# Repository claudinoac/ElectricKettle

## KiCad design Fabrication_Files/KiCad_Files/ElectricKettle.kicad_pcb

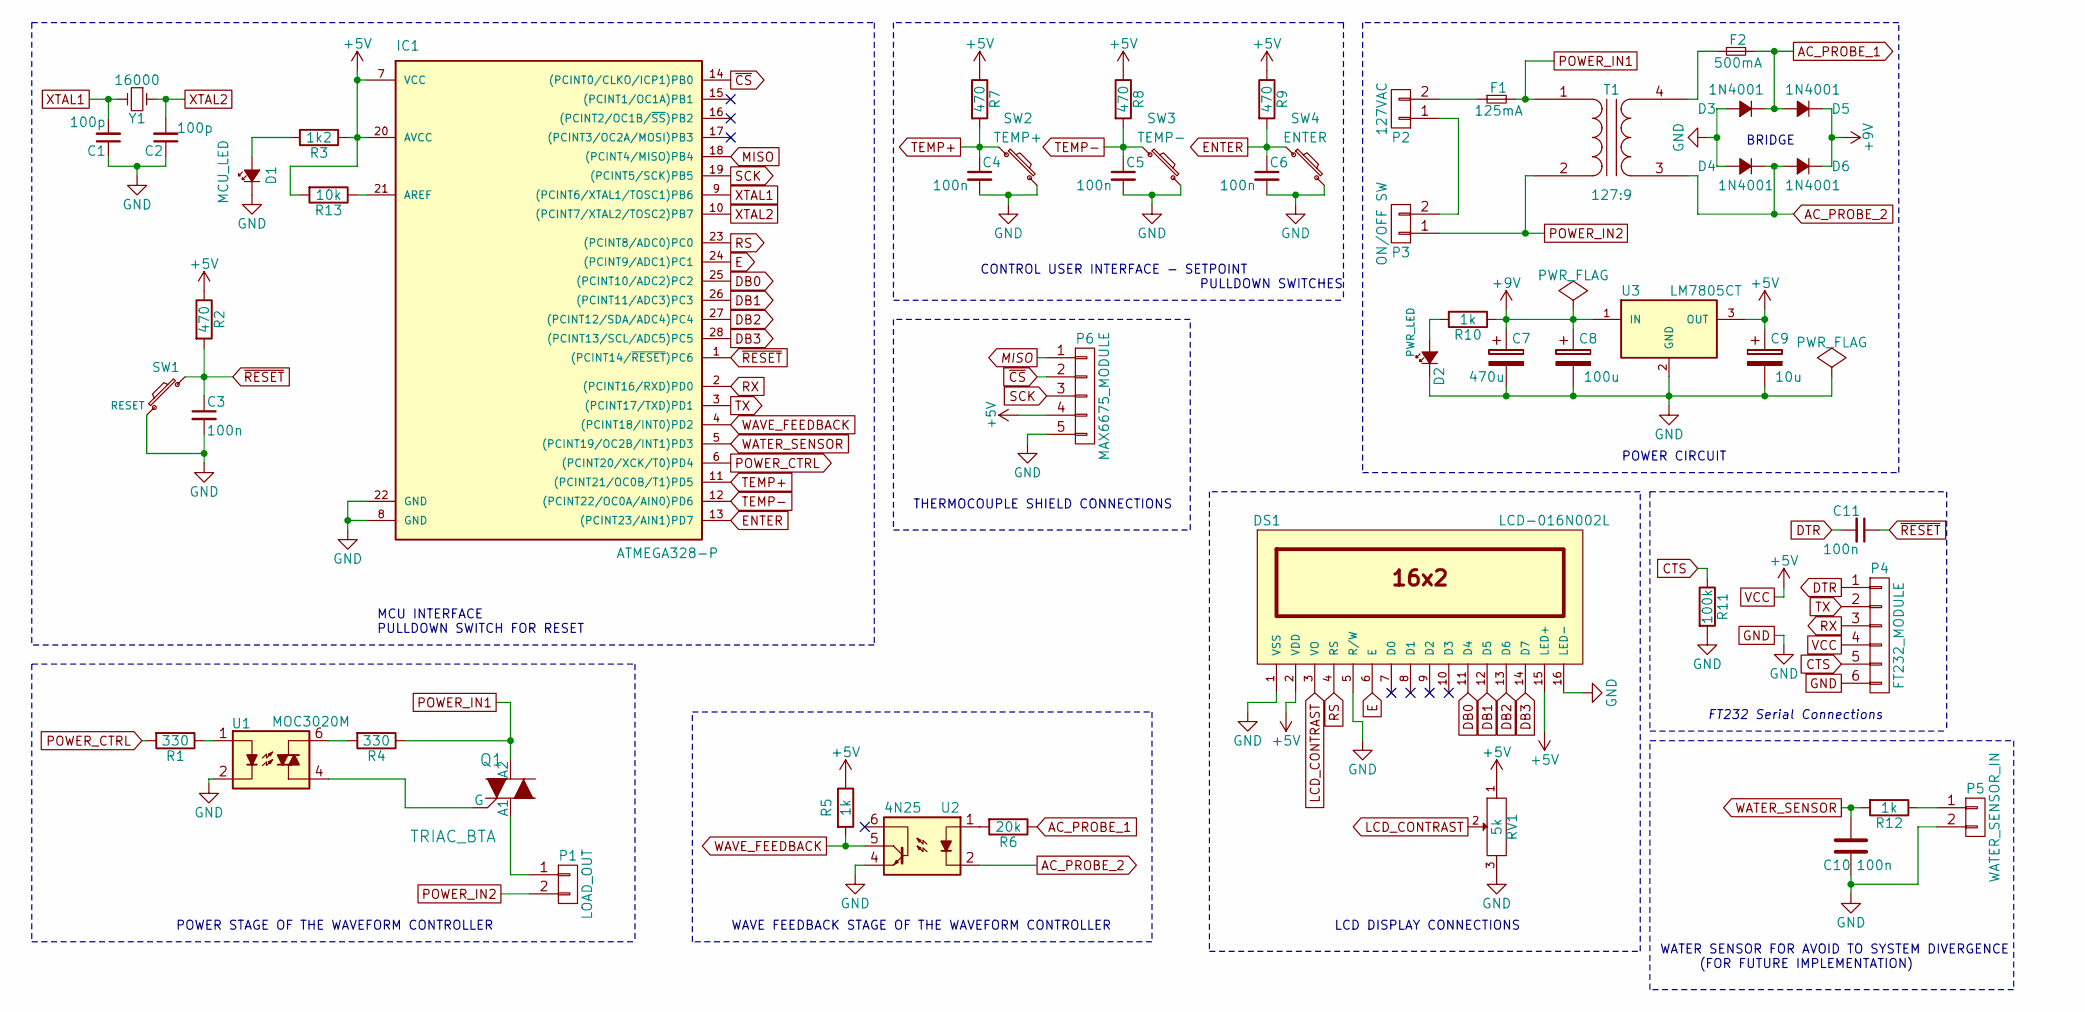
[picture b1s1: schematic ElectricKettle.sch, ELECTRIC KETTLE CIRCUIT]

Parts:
C1, C2: 100p; C_Rect_L7.0mm_W2.0mm_P5.00mm
C3, C4, C5, C6, C10, C11: 100n; C_Rect_L7.0mm_W2.0mm_P5.00mm
C7: 470u; CP_Radial_D10.0mm_P5.00mm
C8: 100u; C_Rect_L7.0mm_W2.0mm_P5.00mm
C9: 10u; CP_Radial_D5.0mm_P2.50mm
D1: MCU_LED; LED_D5.0mm
D2: PWR_LED; LED_D5.0mm
D3, D4, D5, D6: 1N4001; D_DO-35_SOD27_P7.62mm_Horizontal
DS1: LCD-016N002L; WC1602A
F1: 125mA; Fuseholder5x20_horiz_SemiClosed_Casing10x25mm
F2: 500mA; Fuseholder5x20_horiz_SemiClosed_Casing10x25mm
IC1: ATMEGA328-P; DIP-28_W7.62mm_LongPads
P1: LOAD_OUT; bornier2
P2: 127VAC; bornier2
P3: ON/OFF SW; bornier2
P4: FT232_MODULE; Pin_Header_Straight_1x06_Pitch1.27mm
P5: WATER_SENSOR_IN; Pin_Header_Straight_1x02_Pitch1.27mm
P6: MAX6675_MODULE; Pin_Header_Straight_1x05_Pitch1.27mm
Q1: TRIAC_BTA; TO-220_Vertical
R1, R4: 330; RC03
R2, R7, R8, R9: 470; RC03
R3: 1k2; RC03
R5, R10, R12: 1k; RC03
R6: 20k; RC03
R11: 100k; RC03
R13: 10k; RC03
RV1: 5k; Potentiometer_Alps_RK163_Single_Vertical
SW1: RESET; SW_PUSH_6mm
SW2: TEMP+; SW_PUSH_6mm
SW3: TEMP-; SW_PUSH_6mm
SW4: ENTER; SW_PUSH_6mm
T1: 127:9; 9V_transformer
U1: MOC3020M; DIP-6_W7.62mm_LongPads
U2: 4N25; DIP-6_W7.62mm_LongPads
U3: LM7805CT; TO-220_Vertical
Y1: 16000; RC03

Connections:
+9V: C7.1, C8.1, D5.1 (K), D6.1 (K), R10.1, U3.1 (IN)
AC_PROBE_1: D3.1 (K), D5.2 (A), F2.2, R6.1
AC_PROBE_2: D4.1 (K), D6.2 (A), T1.3 (SA), U2.2
CTS: P4.5, R11.1
DB0: DS1.11 (D4), IC1.25 ((PCINT10/ADC2)PC2)
DB1: DS1.12 (D5), IC1.26 ((PCINT11/ADC3)PC3)
DB2: DS1.13 (D6), IC1.27 ((PCINT12/SDA/ADC4)PC4)
DB3: DS1.14 (D7), IC1.28 ((PCINT13/SCL/ADC5)PC5)
DTR: C11.2, P4.1
E: DS1.6 (E), IC1.24 ((PCINT9/ADC1)PC1)
ENTER: C6.1, IC1.13 ((PCINT23/AIN1)PD7), R9.2, SW4.1
GND: C1.1, C2.1, C3.2, C4.2, C5.2, C6.2, C7.2, C8.2, C9.2, C10.2, D1.1 (K), D2.1 (K), D3.2 (A), D4.2 (A), DS1.1 (VSS), DS1.5 (R/W), DS1.16 (LED-), IC1.8 (GND), IC1.22 (GND), P4.6, P5.2, P6.5, R11.2, RV1.3, SW1.1, SW2.2, SW3.2, SW4.2, U1.2, U2.4, U3.2 (GND)
LCD_CONTRAST: DS1.3 (VO), RV1.2
MISO: IC1.18 ((PCINT4/MISO)PB4), P6.1
unnamed: D1.2 (A), R3.2
unnamed: D2.2 (A), R10.2
unnamed: F1.1, P2.2
unnamed: F2.1, T1.4 (SB)
unnamed: IC1.21 (AREF), R13.1
unnamed: P1.1, Q1.3 (A1)
unnamed: P2.1, P3.2
unnamed: P5.1, R12.1
unnamed: Q1.1 (G), U1.4
unnamed: R1.1, U1.1
unnamed: R4.2, U1.6
unnamed: R6.2, U2.1
POWER_CTRL: IC1.6 ((PCINT20/XCK/T0)PD4), R1.2
POWER_IN1: F1.2, Q1.2 (A2), R4.1, T1.1 (AA)
POWER_IN2: P1.2, P3.1, T1.2 (AB)
RS: DS1.4 (RS), IC1.23 ((PCINT8/ADC0)PC0)
RX: IC1.2 ((PCINT16/RXD)PD0), P4.3
SCK: IC1.19 ((PCINT5/SCK)PB5), P6.3
TEMP+: C4.1, IC1.11 ((PCINT21/OC0B/T1)PD5), R7.2, SW2.1
TEMP-: C5.1, IC1.12 ((PCINT22/OC0A/AIN0)PD6), R8.2, SW3.1
TX: IC1.3 ((PCINT17/TXD)PD1), P4.2
VCC: C9.1, DS1.2 (VDD), DS1.15 (LED+), IC1.7 (VCC), IC1.20 (AVCC), P4.4, P6.4, R2.1, R3.1, R5.1, R7.1, R8.1, R9.1, R13.2, RV1.1, U3.3 (OUT)
WATER_SENSOR: C10.1, IC1.5 ((PCINT19/OC2B/INT1)PD3), R12.2
WAVE_FEEDBACK: IC1.4 ((PCINT18/INT0)PD2), R5.2, U2.5
XTAL1: C1.2, IC1.9 ((PCINT6/XTAL1/TOSC1)PB6), Y1.2
XTAL2: C2.2, IC1.10 ((PCINT7/XTAL2/TOSC2)PB7), Y1.1
~CS: IC1.14 ((PCINT0/CLKO/ICP1)PB0), P6.2
~RESET: C3.1, C11.1, IC1.1 ((PCINT14/~RESET~)PC6), R2.2, SW1.2

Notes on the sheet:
POWER STAGE OF THE WAVEFORM CONTROLLER
WAVE FEEDBACK STAGE OF THE WAVEFORM CONTROLLER
LCD DISPLAY CONNECTIONS
CONTROL USER INTERFACE - SETPOINT PULLDOWN SWITCHES
MCU INTERFACE PULLDOWN SWITCH FOR RESET
POWER CIRCUIT
THERMOCOUPLE SHIELD CONNECTIONS
WATER SENSOR FOR AVOID TO SYSTEM DIVERGENCE (FOR FUTURE IMPLEMENTATION)
FT232 Serial Connections
BRIDGE

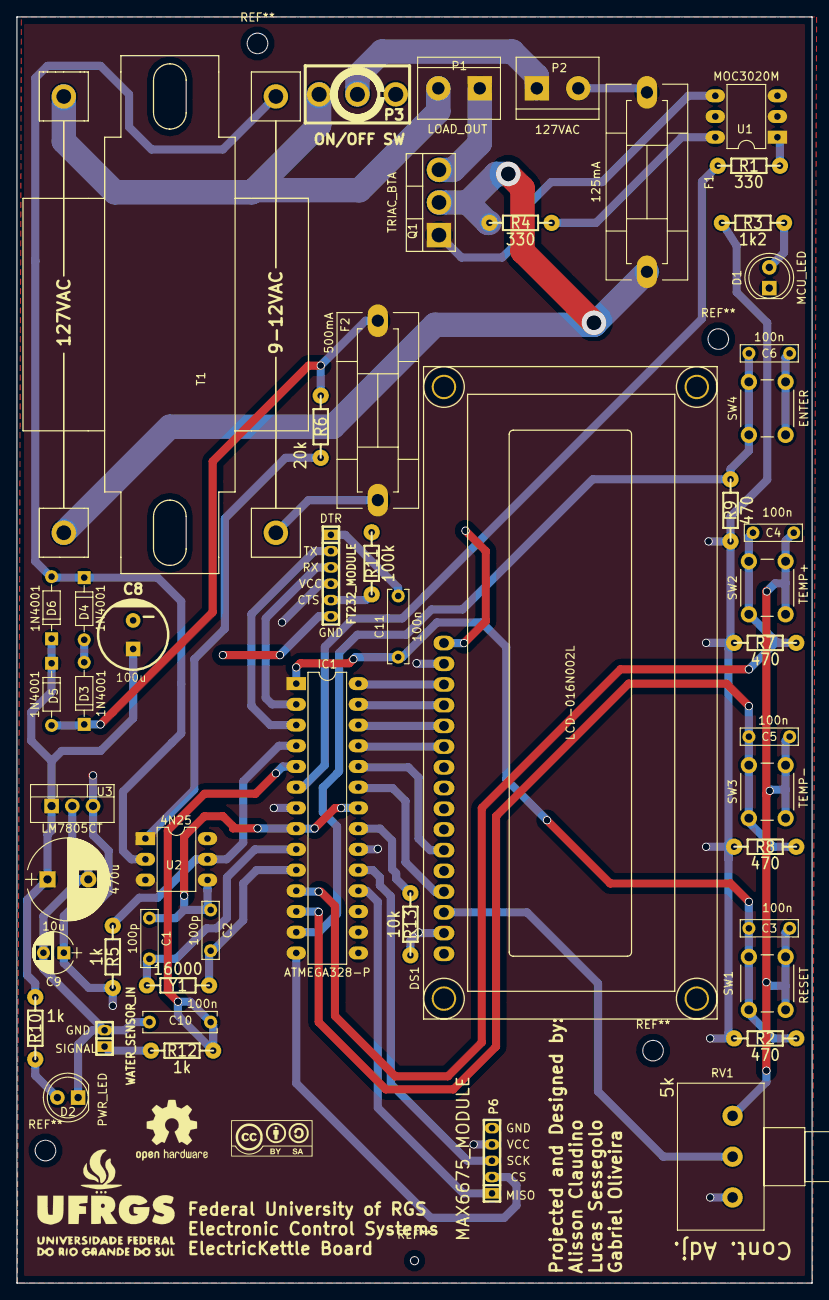
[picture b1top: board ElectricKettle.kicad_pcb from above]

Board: 2 copper layers, 97.5 x 155.2 mm, 51 parts (0 on the bottom side), 42 nets.

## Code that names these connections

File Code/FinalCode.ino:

/*# # # # # # # # # # # # # # # # # # # # # # # # # # # # # # #
# ElectricKettle Code v1.0                                  #
# Authors: Alisson Claudino, Lucas Sessegolo, Gabriel Luis  #
# License: GNU GPLv2                                        #
# # # # # # # # # # # # # # # # # # # # # # # # # # # # # # #
*/
#include <OneWire.h>                        
#include <DallasTemperature.h>
#include <LiquidCrystal.h>


#define POWER_CTRL 4                        //Set TRIAC's action pin
#define WAVE_FEEDBACK 2                     //Set wave feedback's pin
#define ONE_WIRE_BUS 8                      //Set temp sensor's pin

#define TEMP_PLUS 5                         //Set Temp+ pin
#define TEMP_MINUS 6                        //Set Temp- pin
#define ENTER 7                             //Set Enter pin

LiquidCrystal lcd(14, 15, 16, 17, 18, 19);  //Set LCD's pins
OneWire oneWire(ONE_WIRE_BUS);              //Set temp sensor
DallasTemperature sensor(&oneWire);         //Init temp sensor
DeviceAddress insideThermometer;            //Associate temp sensor SPI address

int espera_micro=0;                         //TRIAC's time variable
int cont=0;                                 //Time counter by zero deteccion
int seg=0;                                  //Time counter in seconds
int flag_zero=0;                            //Zero detecction flag
float tempC=-127;                           //Temp variable
int count=0;                                //Array with all values for associate power and triac's shot
int potencias[501]={8333,8325,8317,8308,8300,8292,8283,8275,8267,8258,8250,8242,8233,8225,8217,8208,8200,8192,8183,8175,8167,8158,8150,8141,8133,8125,8116,8108,8100,8091,8083,8074,8066,8058,8049,8041,8032,8024,8015,8007,7998,7990,7981,7973,7964,7956,7947,7939,7930,7922,7913,7905,7896,7888,7879,7870,7862,7853,7845,7836,7827,7819,7810,7801,7793,7784,7775,7767,7758,7749,7740,7732,7723,7714,7705,7696,7688,7679,7670,7661,7652,7643,7634,7625,7616,7607,7598,7589,7580,7571,7562,7553,7544,7535,7526,7516,7507,7498,7489,7480,7470,7461,7452,7442,7433,7424,7414,7405,7395,7386,7376,7367,7357,7348,7338,7328,7319,7309,7299,7290,7280,7270,7260,7250,7240,7230,7220,7210,7200,7190,7180,7170,7160,7150,7139,7129,7119,7108,7098,7087,7077,7066,7056,7045,7035,7024,7013,7002,6991,6980,6969,6958,6947,6936,6925,6914,6903,6891,6880,6868,6857,6845,6834,6822,6810,6798,6786,6774,6762,6750,6738,6726,6713,6701,6688,6676,6663,6650,6637,6624,6611,6598,6585,6571,6558,6544,6530,6516,6503,6488,6474,6460,6445,6431,6416,6401,6386,6371,6356,6340,6324,6309,6292,6276,6260,6243,6226,6209,6192,6174,6156,6138,6120,6101,6083,6063,6044,6024,6004,5983,5962,5940,5919,5896,5873,5850,5826,5801,5776,5750,5723,5695,5667,5637,5607,5575,5542,5507,5470,5432,5391,5348,5301,5251,5195,5133,5063,4980,4876,4729,4167,3605,3458,3354,3271,3200,3138,3083,3032,2986,2942,2902,2863,2827,2792,2759,2727,2696,2667,2638,2611,2584,2558,2532,2508,2484,2460,2438,2415,2393,2372,2351,2330,2310,2290,2270,2251,2232,2214,2195,2177,2159,2142,2125,2107,2091,2074,2057,2041,2025,2009,1994,1978,1963,1948,1932,1918,1903,1888,1874,1859,1845,1831,1817,1803,1790,1776,1763,1749,1736,1723,1710,1697,1684,1671,1658,1646,1633,1621,1608,1596,1584,1571,1559,1547,1535,1524,1512,1500,1488,1477,1465,1454,1442,1431,1420,1409,1397,1386,1375,1364,1353,1342,1331,1321,1310,1299,1288,1278,1267,1257,1246,1236,1225,1215,1205,1194,1184,1174,1164,1153,1143,1133,1123,1113,1103,1093,1083,1074,1064,1054,1044,1034,1025,1015,1005,996,986,976,967,957,948,938,929,919,910,901,891,882,873,863,854,845,836,826,817,808,799,790,781,772,762,753,744,735,726,717,708,699,691,682,673,664,655,646,637,628,620,611,602,593,585,576,567,558,550,541,532,524,515,506,498,489,480,472,463,455,446,437,429,420,412,403,395,386,378,369,361,352,344,335,327,318,310,301,293,285,276,268,259,251,243,234,226,217,209,201,192,184,175,167,159,150,142,134,125,117,109,100,92,84,75,67,59,50,42,34,25,17,9,0};
int potencia=500;                           //Power variable
boolean sampling_flag=false,set_flag=false,out_flag=false; //Auxiliary flags
float temp_set=52;                                         //Temp set variable
float temp_req=52;                                         //Temp req variable
float error=10000;                                         //PI controller error variable
float ui=0;                                                //Controller's integral time constant
float error_ant=10000;                                     //PI previous error value variable
float ui_ant=0;                                            //PI previous integral time constant variable
float up=1;                                                //PI proportional value variable
                                                              



void ZeroCross() //Zero-Crossing function
{
  detachInterrupt(0);                     //disables interruptions to avoid divergence
  delayMicroseconds(espera_micro);        //Wait required time before shot
  digitalWrite(POWER_CTRL,HIGH);          //TRIAC's first shot
  delayMicroseconds(50);
  digitalWrite(POWER_CTRL,LOW);
  delayMicroseconds(8333-50);             //Wait until the next semicycle begins
  digitalWrite(POWER_CTRL,HIGH);          //TRIAC's second shot
  delayMicroseconds(50);
  digitalWrite(POWER_CTRL,LOW);
  cont++;                                   //Increase counter
  if(cont==120)                             //If counter = 120, 1 second have been passed
  {                            
    cont=0;                                 //Clear counter
    seg++;                                  //Increase seconds counter
    if(seg%6==0)
      sampling_flag=true;
    if(seg%2==0)
      set_flag=true;
      
    out_flag=sampling_flag|set_flag;
  }
  if(!(out_flag))
    attachInterrupt(0,ZeroCross,RISING);
}

int Tabela_Tempo(int pot)
{                   //Função que converte a potência no tempo de espera de acordo com a tabela calculada
  int tempo;
  tempo=potencias[pot+1];                    //A tabela é um array de 501 números, o primeiro número equivale à potência zero e assim por diante
  return tempo;  
  
}

void setup() 
{
  Serial.begin(9600);
  lcd.begin(16,2);
  sensor.begin();
  sensor.getDeviceCount();
  sensor.getAddress(insideThermometer, 0);
  sensor.setResolution(insideThermometer, 12);
  lcd.println("Iniciando...");
  lcd.clear();
  if (sensor.isParasitePowerMode()) 
    lcd.println("Sensor Encontrado!");
  else lcd.println("error! Sensor não encontrado!");
  delay(1000);
  lcd.clear();
  pinMode(TEMP_PLUS,INPUT);
  pinMode(TEMP_MINUS,INPUT);
  pinMode(ENTER,INPUT);
  pinMode(WAVE_FEEDBACK,INPUT);             //Pino dois ligado no circuito de detecção de passagem de zero (input)
  pinMode(POWER_CTRL,OUTPUT);               //Pino quatro ligado ao controle de potência (output)
  attachInterrupt(0,ZeroCross,RISING);        //Interrupt number 0 == pino 2 //interrupt quando detecta passagem de zero
  espera_micro=Tabela_Tempo(potencia);      //Valor de inicialização de 250W
  readSensor();
  LCD();
  chooseTemp();
  }

void LCD()
{
   lcd.clear();
   lcd.print("P=");
   lcd.print(potencia);
   lcd.print(" T=");
   lcd.print(tempC);
   lcd.setCursor(0,2);
   lcd.print("T_set=");
   lcd.print(temp_set);
   lcd.print("/");
   lcd.print(temp_req);
  
  }
  
void readSensor()
{
  do
  {
    sensor.requestTemperatures();
    tempC = sensor.getTempCByIndex(0);
  }
  while((int)tempC==-127);
}

void setPotencia(int pot)
{
  if(!(pot>500 || pot<34))
  { 
    potencia=pot;
  }
  if(potencia<250)
  {
     espera_micro=Tabela_Tempo(potencia); 
  }
  else
  {
    espera_micro=Tabela_Tempo(potencia)+650;
  }
}

void setTemp(int temp)
{
  if(temp>=52)
    temp_set=temp;
  else
    temp_set=52;
}

void chooseTemp()
{
  if(digitalRead(TEMP_PLUS)==LOW)
   {
     temp_req++;
   }
   if(digitalRead(TEMP_MINUS)==LOW)
   {
     temp_req--;
   }
}

void Control()
{
   error=temp_set-tempC;
   if(temp_set<52 && error>3)
   {
     setPotencia(500);
   }
   else
   {
     if((temp_set<=52 && error<=3))
     {
        setPotencia(34);
     }
     else
     {  
        if(temp_set>52 && error>6)
        {
           setPotencia(500);
           
           
        }
        else if(error<=6)
        {
          lcd.setCursor(13,0);
          lcd.print("!!!");
          up=74.47*error;
          
          if((up+ui+34)>=34)
          {
            setPotencia(up+ui+34);
          }
          else
            setPotencia(34);
        }
        ui=8,595*(error+error_ant)+ui_ant;
        ui_ant=ui;
        error_ant=error;
      }
    }
}
void loop() 
{
  detachInterrupt(0);
  LCD();
  chooseTemp();
  if(digitalRead(ENTER)==LOW)
  {
    setTemp(temp_req);
  }
  if(sampling_flag==true)
  {
    readSensor();
    Control();
    sampling_flag=false;
  }
  set_flag=false;
  out_flag=false;
  attachInterrupt(0,ZeroCross,RISING);
  delay(300);
}

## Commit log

2017-11-20 First Commit: Added partial circuit schematic
2017-11-21 Complete Schematic V0.1
2017-11-23 ADD: Water Sensor Filter and Socket for Future Implementation
2018-02-07 ADD: All Fabrication Files
2018-02-07 ADD: Project's Documentation
2018-02-07 ADD: Final Code w/ some comments (incomplete)
2018-02-07 EDIT: Folder Organization
2018-04-23 EDIT: git attributes
